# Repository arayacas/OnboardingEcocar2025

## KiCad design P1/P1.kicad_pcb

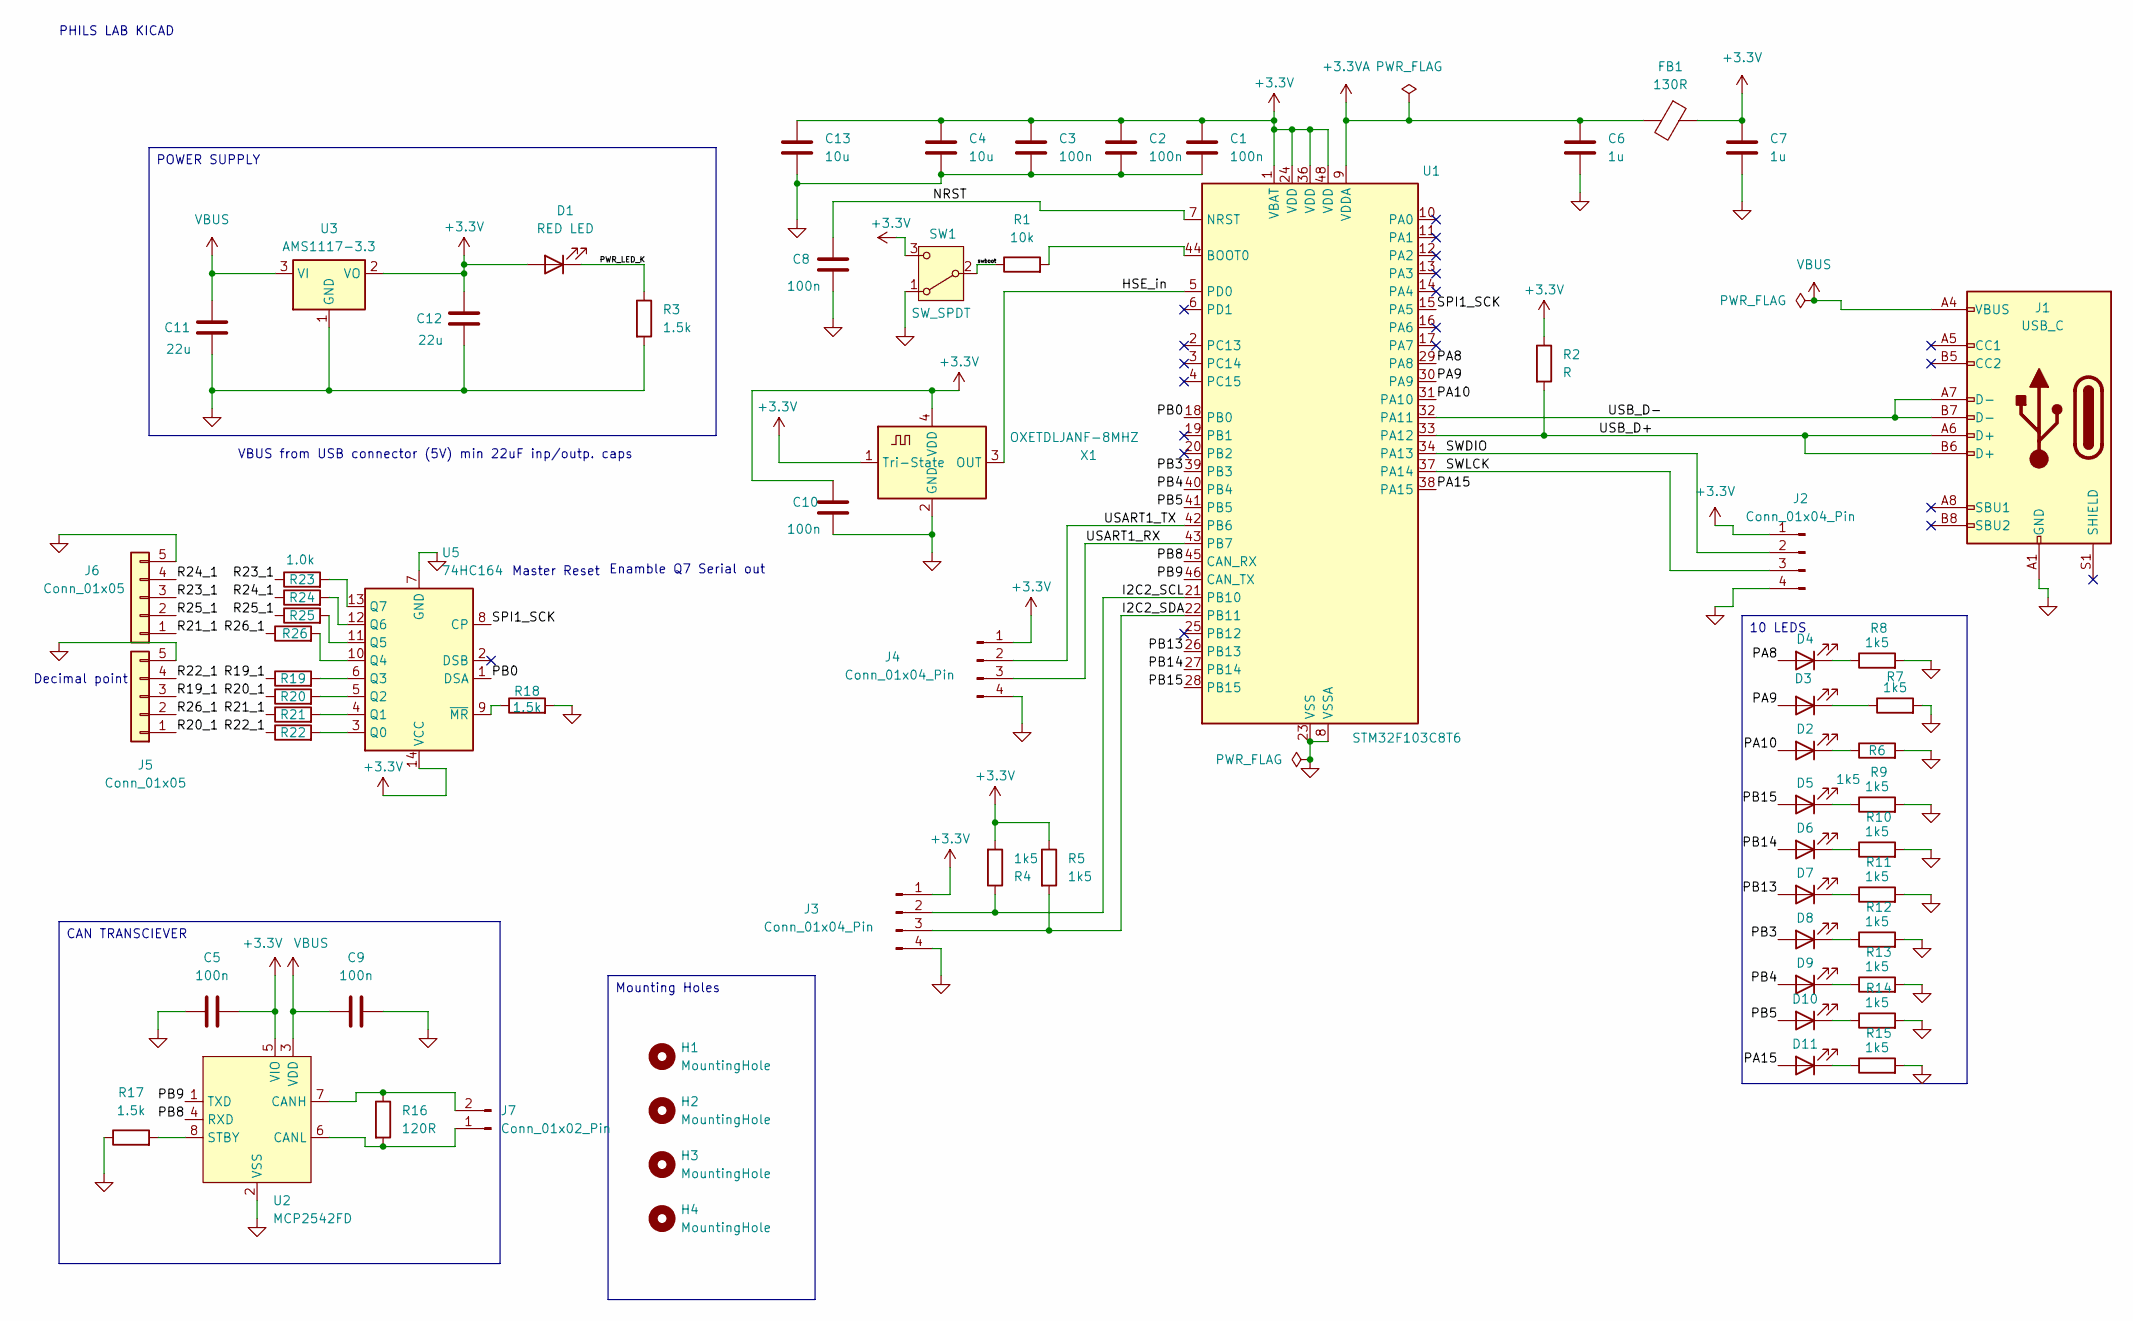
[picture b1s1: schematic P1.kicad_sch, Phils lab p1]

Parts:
C1, C2, C3, C5, C8, C9, C10: 100n; C_0603_1608Metric
C4, C13: 10u; C_0603_1608Metric
C6, C7: 1u; C_0603_1608Metric
C11, C12: 22u; C_0805_2012Metric
D1, D2, D3, D4, D5, D6, D7, D8, D9, D10, D11: RED LED; LED_0603_1608Metric
FB1: 130R; L_0603_1608Metric
H1, H2, H3, H4: MountingHole; MountingHole_2.2mm_M2
J1: USB_C; USB_C_Receptacle_GCT_USB4105-xx-A_16P_TopMnt_Horizontal
J2, J3, J4: Conn_01x04_Pin; PinHeader_1x04_P2.54mm_Vertical
J5, J6: Conn_01x05; PinHeader_1x05_P2.54mm_Vertical
J7: Conn_01x02_Pin; PinHeader_1x02_P2.00mm_Vertical
R1: 10k; R_0603_1608Metric
R2: R; R_0603_1608Metric
R3, R17, R18, R19, R20, R21, R22, R23, R24, R25: 1.5k; R_0603_1608Metric
R4, R5, R6, R7, R8, R9, R10, R11, R12, R13, R14, R15: 1k5; R_0603_1608Metric
R16: 120R; R_0603_1608Metric
R26: 1.0k; R_0603_1608Metric
SW1: SW_SPDT; SW_SPDT_PCM12
U1: STM32F103C8T6; LQFP-48_7x7mm_P0.5mm
U2: MCP2542FD; SOIC-8_3.9x4.9mm_P1.27mm
U3: AMS1117-3.3; SOT-223-3_TabPin2
U5: 74HC164; TSSOP-14_4.4x5mm_P0.65mm
X1: OXETDLJANF-8MHZ; Crystal_SMD_3225-4Pin_3.2x2.5mm

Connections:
+3.3V: C1.1, C2.1, C3.1, C4.1, C5.2, C7.1, C10.1, C12.1, C13.1, D1.2 (A), FB1.1, J2.1, J3.1, J4.1, R2.1, R4.2, R5.1, SW1.3 (C), U1.1 (VBAT), U1.24 (VDD), U1.36 (VDD), U1.48 (VDD), U2.5 (VIO), U3.2 (VO), U5.14 (VCC), X1.1 (Tri-State), X1.4 (VDD)
+3.3VA: C6.1, FB1.2, U1.9 (VDDA)
/HSE_in: U1.5 (PD0), X1.3 (OUT)
/I2C2_SCL: J3.2, R4.1, U1.21 (PB10)
/I2C2_SDA: J3.3, R5.2, U1.22 (PB11)
/NRST: C8.1, U1.7 (NRST)
/PA8: D4.2 (A), U1.29 (PA8)
/PA9: D3.2 (A), U1.30 (PA9)
/PA10: D2.2 (A), U1.31 (PA10)
/PA15: D11.2 (A), U1.38 (PA15)
/PB0: U1.18 (PB0), U5.1 (DSA)
/PB3: D8.2 (A), U1.39 (PB3)
/PB4: D9.2 (A), U1.40 (PB4)
/PB5: D10.2 (A), U1.41 (PB5)
/PB8: U1.45 (CAN_RX), U2.4 (RXD)
/PB9: U1.46 (CAN_TX), U2.1 (TXD)
/PB13: D7.2 (A), U1.26 (PB13)
/PB14: D6.2 (A), U1.27 (PB14)
/PB15: D5.2 (A), U1.28 (PB15)
/PWR_LED_K: D1.1 (K), R3.1
/R19_1: J5.3, R19.1
/R20_1: J5.1, R20.1
/R21_1: J6.1, R21.1
/R22_1: J5.4, R22.1
/R23_1: J6.3, R23.1
/R24_1: J6.4, R24.1
/R25_1: J6.2, R25.1
/R26_1: J5.2, R26.1
/SPI1_SCK: U1.15 (PA5), U5.8 (CP)
/SWDIO: J2.2, U1.34 (PA13)
/SWLCK: J2.3, U1.37 (PA14)
/USART1_RX: J4.3, U1.43 (PB7)
/USART1_TX: J4.2, U1.42 (PB6)
/USB_D+: J1.A6 (D+), J1.B6 (D+), R2.2, U1.33 (PA12)
/USB_D-: J1.A7 (D-), J1.B7 (D-), U1.32 (PA11)
/swboot: R1.1, SW1.2 (B)
GND: C1.2, C2.2, C3.2, C4.2, C5.1, C6.2, C7.2, C8.2, C9.2, C10.2, C11.2, C12.2, C13.2, J1.A1 (GND), J1.A12 (GND), J1.B1 (GND), J1.B12 (GND), J2.4, J3.4, J4.4, J5.5, J6.5, R3.2, R6.2, R7.2, R8.2, R9.2, R10.2, R11.2, R12.2, R13.2, R14.2, R15.2, R17.1, R18.2, SW1.1 (A), U1.8 (VSSA), U1.23 (VSS), U1.35 (VSS), U1.47 (VSS), U2.2 (VSS), U3.1 (GND), U5.7 (GND), X1.2 (GND)
unnamed: D2.1 (K), R6.1
unnamed: D3.1 (K), R7.1
unnamed: D4.1 (K), R8.1
unnamed: D5.1 (K), R9.1
unnamed: D6.1 (K), R10.1
unnamed: D7.1 (K), R11.1
unnamed: D8.1 (K), R12.1
unnamed: D9.1 (K), R13.1
unnamed: D10.1 (K), R14.1
unnamed: D11.1 (K), R15.1
unnamed: J7.1, R16.2, U2.6 (CANL)
unnamed: J7.2, R16.1, U2.7 (CANH)
unnamed: R1.2, U1.44 (BOOT0)
unnamed: R17.2, U2.8 (STBY)
unnamed: R22.2, U5.3 (Q0)
unnamed: R21.2, U5.4 (Q1)
unnamed: R20.2, U5.5 (Q2)
unnamed: R19.2, U5.6 (Q3)
unnamed: R26.2, U5.10 (Q4)
unnamed: R25.2, U5.11 (Q5)
unnamed: R24.2, U5.12 (Q6)
unnamed: R23.2, U5.13 (Q7)
unnamed: R18.1, U5.9 (~MR)
VBUS: C9.1, C11.1, J1.A4 (VBUS), J1.A9 (VBUS), J1.B4 (VBUS), J1.B9 (VBUS), U2.3 (VDD), U3.3 (VI)

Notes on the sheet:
Decimal point
Enamble Q7 Serial out
Master Reset
VBUS from USB connector (5V) min 22uF inp/outp. caps
PHILS LAB KICAD
CAN TRANSCIEVER
POWER SUPPLY
10 LEDS
Mounting Holes

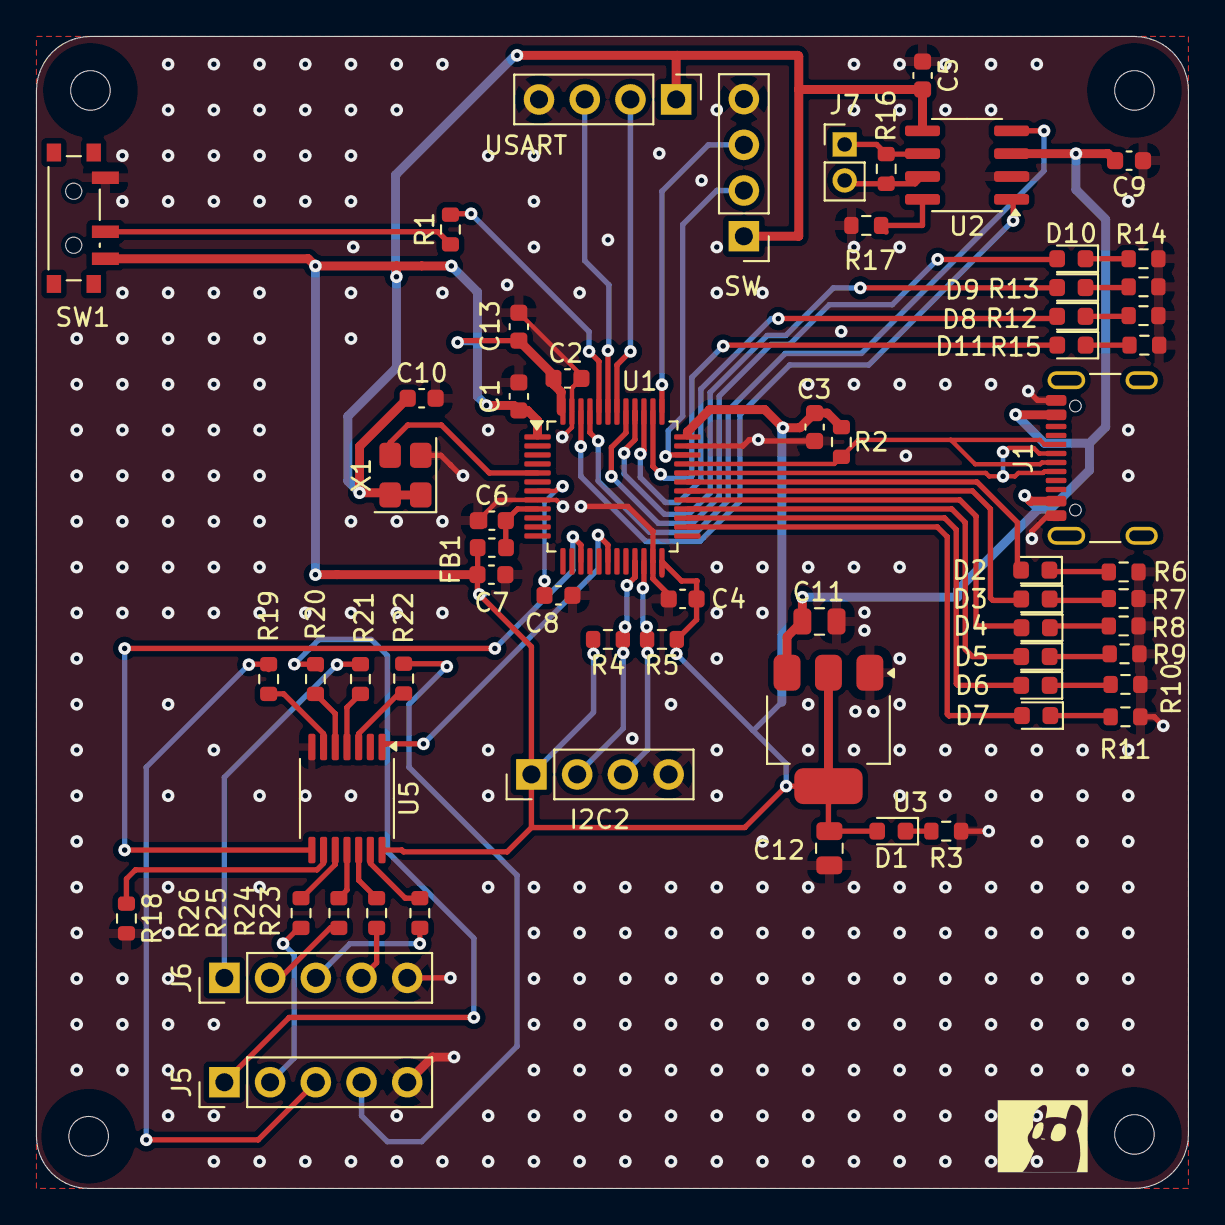
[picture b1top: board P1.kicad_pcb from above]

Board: 2 copper layers, 64.0 x 64.0 mm, 68 parts (0 on the bottom side), 61 nets.

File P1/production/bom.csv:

Designator,Footprint,Quantity,Value,LCSC Part #
"C1, C2, C3",0402,3,100n,
"C10, C5, C8, C9",0603,4,100n,
"C11, C12",0805,2,22u,
"C13, C4",0603,2,10u,
C6,0402,1,1u,
C7,0603,1,1u,
"D1, D10, D11, D2, D3, D4, D5, D6, D7, D8, D9",0603,11,RED LED,
FB1,0603,1,130R,
J1,USB_C_Receptacle_GCT_USB4105-xx-A_16P_TopMnt_Horizontal,1,USB_C,
"J2, J3, J4",PinHeader_1x04_P2.54mm_Vertical,3,Conn_01x04_Pin,
"J5, J6",PinHeader_1x05_P2.54mm_Vertical,2,Conn_01x05,
J7,PinHeader_1x02_P2.00mm_Vertical,1,Conn_01x02_Pin,
R1,0603,1,10k,
"R10, R11, R12, R13, R14, R15, R4, R5, R6, R7, R8, R9",0603,12,1k5,
R16,0603,1,120R,
"R17, R18, R19, R20, R21, R22, R23, R24, R25, R3",0603,10,1.5k,
R2,0603,1,R,
R26,0603,1,1.0k,
SW1,SW_SPDT_PCM12,1,SW_SPDT,
U1,LQFP-48_7x7mm_P0.5mm,1,STM32F103C8T6,
U2,SOIC-8_3.9x4.9mm_P1.27mm,1,MCP2542FD,
U3,SOT-223-3_TabPin2,1,AMS1117-3.3,
U5,TSSOP-14_4.4x5mm_P0.65mm,1,74HC164,
X1,Crystal_SMD_3225-4Pin_3.2x2.5mm,1,OXETDLJANF-8MHZ,

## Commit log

2025-10-29 First upload
2025-10-29 Reviewed version for manufacture
2025-11-01 Rename Onbarding_project_JP_PCB.zip to Onbarding_project_JP_PCB_GERBER.zip
    Geber file rename
2025-11-01 Owen Spotted an error, fix
